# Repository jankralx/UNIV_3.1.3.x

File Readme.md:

UNIV 3.1.3.x
============

BUTTON MODULE - 14 close/open inputs, 1-wire temperature sensor, thermostat, temperature controller

Device webpage: http://hapcan.com/devices/universal/univ_3/univ_3-1-3-x/

Hardware created in Eagle PCB Software http://www.cadsoftusa.com/

Firmware created in Microchip MPLAB http://www.microchip.com/mplabide/ in assembly language

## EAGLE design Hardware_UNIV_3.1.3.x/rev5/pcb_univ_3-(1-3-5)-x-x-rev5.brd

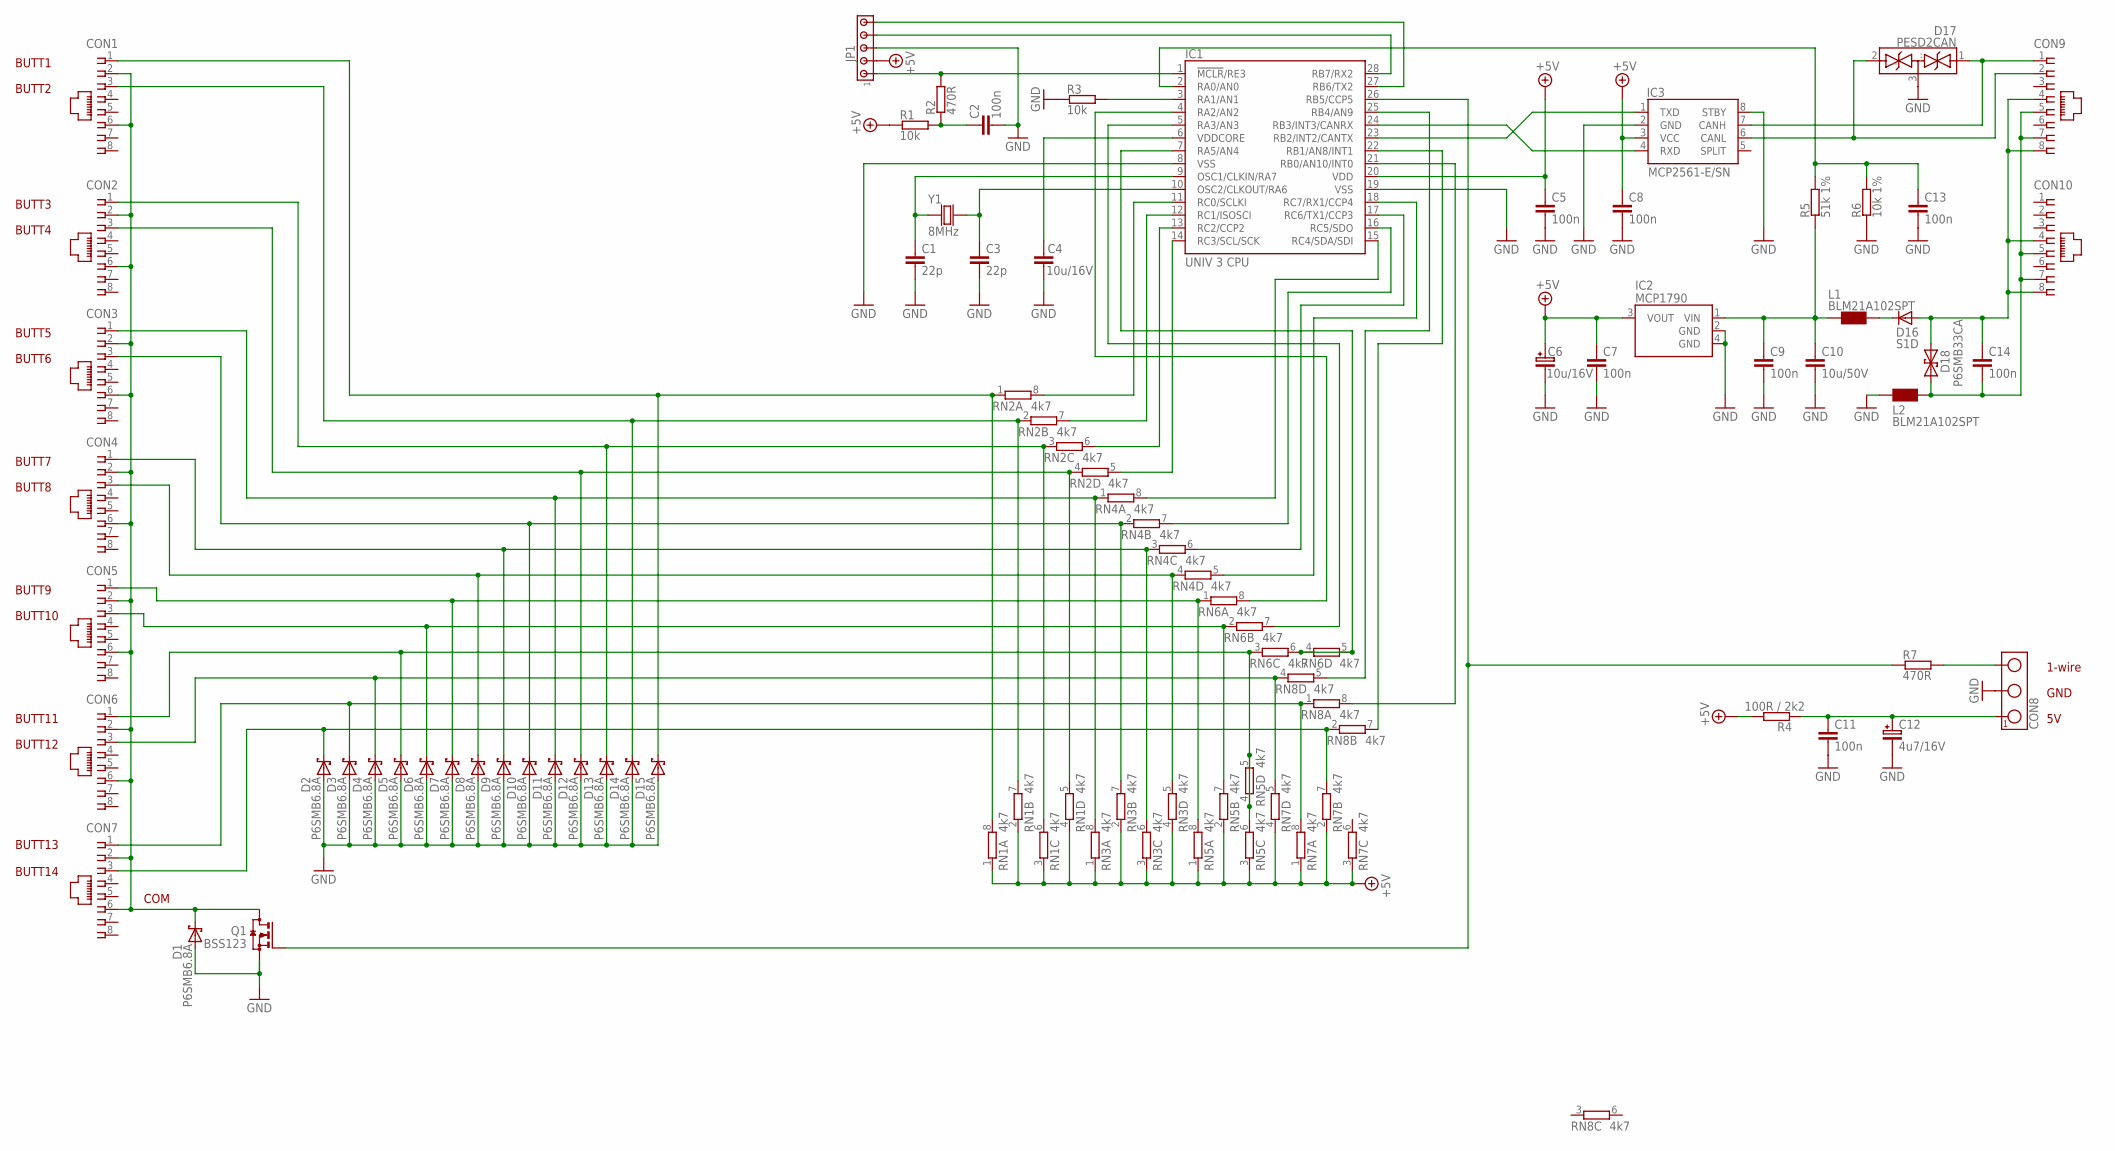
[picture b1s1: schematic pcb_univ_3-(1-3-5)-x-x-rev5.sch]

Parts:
C1, C3: 22p; 0805
C2, C5, C7, C8, C9, C11, C13, C14: 100n; 0805
C4: 10u/16V; 0805
C6: 10u/16V; SMC_B
C10: 10u/50V; 1210
C12: 4u7/16V; SMC_B
CON1, CON2, CON3, CON4, CON5, CON6, CON7, CON9, CON10: RJ45-SOCKET; RJ45-PCB-SOCKET
CON8: TERMINAL-3; ARK3-5X10.5MM
D1, D2, D3, D4, D5, D6, D7, D8, D9, D10, D11, D12, D13, D14, D15: P6SMB6.8A; DO-214
D16: S1D; DO-214
D17: PESD2CAN; SOT-23
D18: P6SMB33CA; DO-214_TRANSIL2
IC1: UNIV 3 CPU; UNIV3CPU
IC2: MCP1790; SOT-223
IC3: MCP2561-E/SN; SO-08
JP1: HEADER5; SIP-5
L1, L2: BLM21A102SPT; 0805@1
Q1: BSS123; SOT23
R1, R3: 10k; 0805
R2, R7: 470R; 0805
R4: 100R / 2k2; 0805
R5: 51k 1%; 0805
R6: 10k 1%; 0805
RN1, RN2, RN3, RN4, RN5, RN6, RN7, RN8: 4k7; EXB38V
Y1: 8MHz; CRYSTAL-HC49V

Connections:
+5V: C5.1, C6.+ (1), C7.1, C8.1, IC1.20 (VDD), IC2.3 (VOUT), IC3.3 (VCC), JP1.2, R1.1, R4.1, RN1.1, RN1.2 (1), RN1.3 (1), RN1.4 (1), RN3.1, RN3.2 (1), RN3.3 (1), RN3.4 (1), RN5.1, RN5.2 (1), RN5.3 (1), RN7.1, RN7.2 (1), RN7.3 (1), RN7.4 (1)
GND: C1.2, C2.2, C3.2, C4.2, C5.2, C6.- (2), C7.2, C8.2, C9.2, C10.2, C11.2, C12.- (2), C13.2, CON8.2, D1.A, D2.A, D3.A, D4.A, D5.A, D6.A, D7.A, D8.A, D9.A, D10.A, D11.A, D12.A, D13.A, D14.A, D15.A, D17.3 (...), IC1.8 (VSS), IC1.19 (VSS), IC2.2 (GND), IC2.4 (GND), IC3.2 (GND), IC3.8 (STBY), JP1.3, L2.1, Q1.2 (S), R3.1, R6.1
unnamed: IC1.26 (RB5/CCP5), Q1.1 (G), R7.1
unnamed: IC1.24 (RB3/INT3/CANRX), IC3.4 (RXD)
unnamed: IC1.23 (RB2/INT2/CANTX), IC3.1 (TXD)
unnamed: IC1.7 (RA5/AN4), RN6.4 (1), RN6.5 (2), RN6.6 (2)
unnamed: CON1.1, D15.C, RN1.8 (2), RN2.1
unnamed: CON2.1, D13.C, RN1.6 (2), RN2.3 (1)
unnamed: C2.1, R1.2, R2.1
unnamed: IC1.1 (!MCLR!/RE3), JP1.1, R2.2
unnamed: CON9.1, D17.1 (.), IC3.7 (CANH)
unnamed: IC1.28 (RB7/RX2), JP1.4
unnamed: IC1.22 (RB1/AN8/INT1), RN8.7 (2)
unnamed: IC1.3 (RA1/AN1), R3.2
unnamed: CON5.1, D7.C, RN5.8 (2), RN6.1
unnamed: IC1.27 (RB6/TX2), JP1.5
unnamed: C3.1, IC1.10 (OSC2/CLKOUT/RA6), Y1.2
unnamed: C13.1, IC1.2 (RA0/AN0), R5.2, R6.2
unnamed: C9.1, C10.1, IC2.1 (VIN), L1.1, R5.1
unnamed: IC1.21 (RB0/AN10/INT0), RN8.8 (2)
unnamed: CON1.3, D14.C, RN1.7 (2), RN2.2 (1)
unnamed: IC1.25 (RB4/AN9), RN8.5 (2)
unnamed: CON2.3, D12.C, RN1.5 (2), RN2.4 (1)
unnamed: IC1.14 (RC3/SCL/SCK), RN2.5 (2)
unnamed: CON3.3, D10.C, RN3.7 (2), RN4.2 (1)
unnamed: CON4.1, D9.C, RN3.6 (2), RN4.3 (1)
unnamed: IC1.11 (RC0/SCLKI), RN2.8 (2)
unnamed: IC1.12 (RC1/ISOSCI), RN2.7 (2)
unnamed: IC1.13 (RC2/CCP2), RN2.6 (2)
unnamed: CON5.3, D6.C, RN5.7 (2), RN6.2 (1)
unnamed: IC1.15 (RC4/SDA/SDI), RN4.8 (2)
unnamed: CON8.3, R7.2
unnamed: CON3.1, D11.C, RN3.8 (2), RN4.1
unnamed: CON4.3, D8.C, RN3.5 (2), RN4.4 (1)
unnamed: IC1.5 (RA3/AN3), RN6.7 (2)
unnamed: IC1.4 (RA2/AN2), RN6.8 (2)
unnamed: CON6.1, D5.C, RN5.4 (1), RN5.5 (2), RN5.6 (2), RN6.3 (1)
unnamed: C11.1, C12.+ (1), CON8.1, R4.2
unnamed: CON6.3, D4.C, RN7.5 (2), RN8.4 (1)
unnamed: C14.2, CON9.5, CON9.7, CON10.5, CON10.7, D18.C (2), L2.2
unnamed: C1.1, IC1.9 (OSC1/CLKIN/RA7), Y1.1
unnamed: CON7.3, D2.C, RN7.7 (2), RN8.2 (1)
unnamed: CON9.2, D17.2 (..), IC3.6 (CANL)
unnamed: IC1.16 (RC5/SDO), RN4.7 (2)
unnamed: IC1.17 (RC6/TX1/CCP3), RN4.6 (2)
unnamed: IC1.18 (RC7/RX1/CCP4), RN4.5 (2)
unnamed: CON7.1, D3.C, RN7.8 (2), RN8.1
unnamed: CON1.2, CON1.6, CON2.2, CON2.6, CON3.2, CON3.6, CON4.2, CON4.6, CON5.2, CON5.6, CON6.2, CON6.6, CON7.2, CON7.6, D1.C, Q1.3 (D)
unnamed: C4.1, IC1.6 (VDDCORE)
unnamed: C14.1, CON9.4, CON9.8, CON10.4, CON10.8, D16.A, D18.A (1)
unnamed: D16.C, L1.2

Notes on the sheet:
BUTT2
BUTT3
BUTT4
BUTT5
BUTT6
COM
BUTT1
BUTT7
BUTT8
1-wire
GND
BUTT9
BUTT10
BUTT11
BUTT12
BUTT14
BUTT13

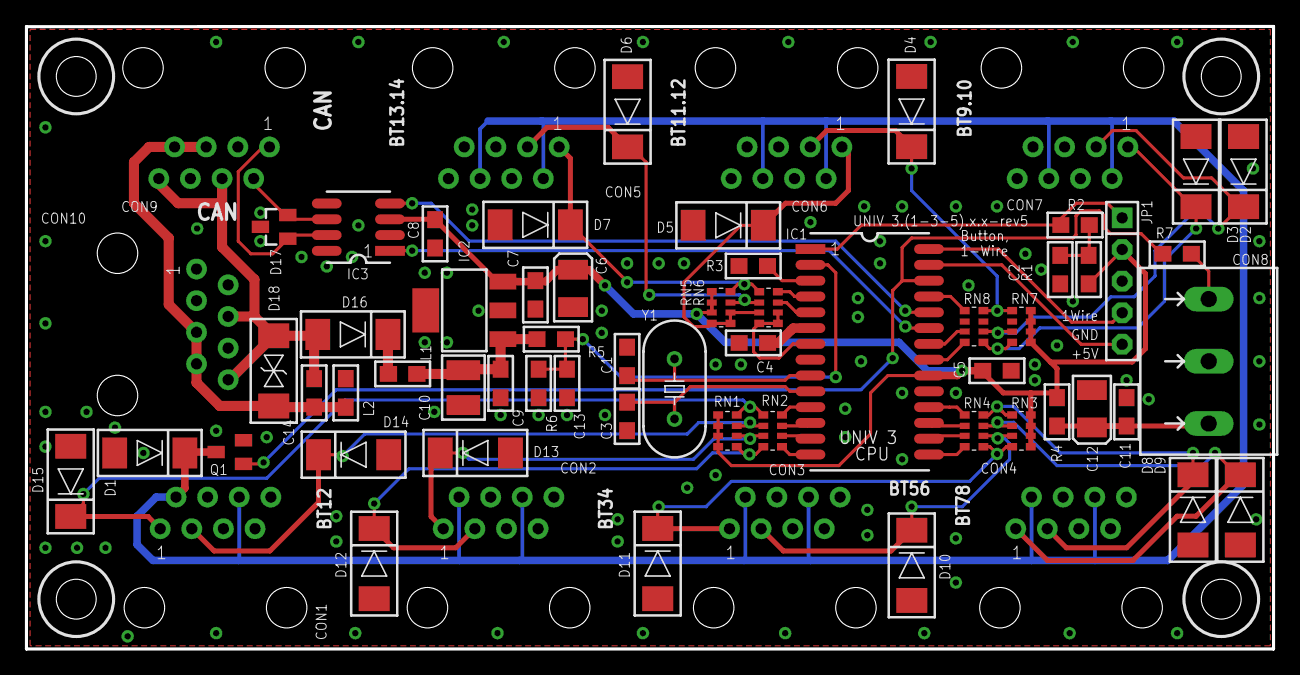
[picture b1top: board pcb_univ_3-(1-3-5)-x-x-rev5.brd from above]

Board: 2 copper layers, 100.2 x 50.0 mm, 65 parts (0 on the bottom side), 51 nets.

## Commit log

2014-05-23 hardware UNIV 3.1.3.x revision 3
2014-06-09 firmware UNIV 3.1.3.0 revision 0
2014-12-07 hardware UNIV 3.1.3.x revision 4
2016-05-03 firmware UNIV 3.1.3.0 revision 1
2016-10-29 firmware UNIV 3.1.3.0 revision 2
2017-06-05 firmware UNIV 3.1.3.1 revision 0
2017-06-11 firmware UNIV 3.1.3.1 revision 1
2022-10-31 firmware UNIV 3.1.3.1 revision 2
2022-10-31 MIT license
2024-07-04 (hardware) rev5 input module with RJ-45 connectors for two buttons connected via a single cable
